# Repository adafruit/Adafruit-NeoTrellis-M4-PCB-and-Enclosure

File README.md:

# Adafruit-NeoTrellis-M4-PCB-and-Enclosure
CAD files for the Adafruit NeoTrellis M4 PCB and Enclosure

PCB format is EagleCAD schematic and board layout
Enclosure format is Illustrator, cut from 3mm Acrylic

For more details, check out the product pages at

   * https://www.adafruit.com/product/4020
   * https://www.adafruit.com/product/3938
   * https://www.adafruit.com/product/3963

Adafruit invests time and resources providing this open source design, 
please support Adafruit and open-source hardware by purchasing 
products from Adafruit!

Designed by Adafruit Industries.  
Creative Commons Attribution, Share-Alike license, check license.txt for more information
All text above must be included in any redistribution

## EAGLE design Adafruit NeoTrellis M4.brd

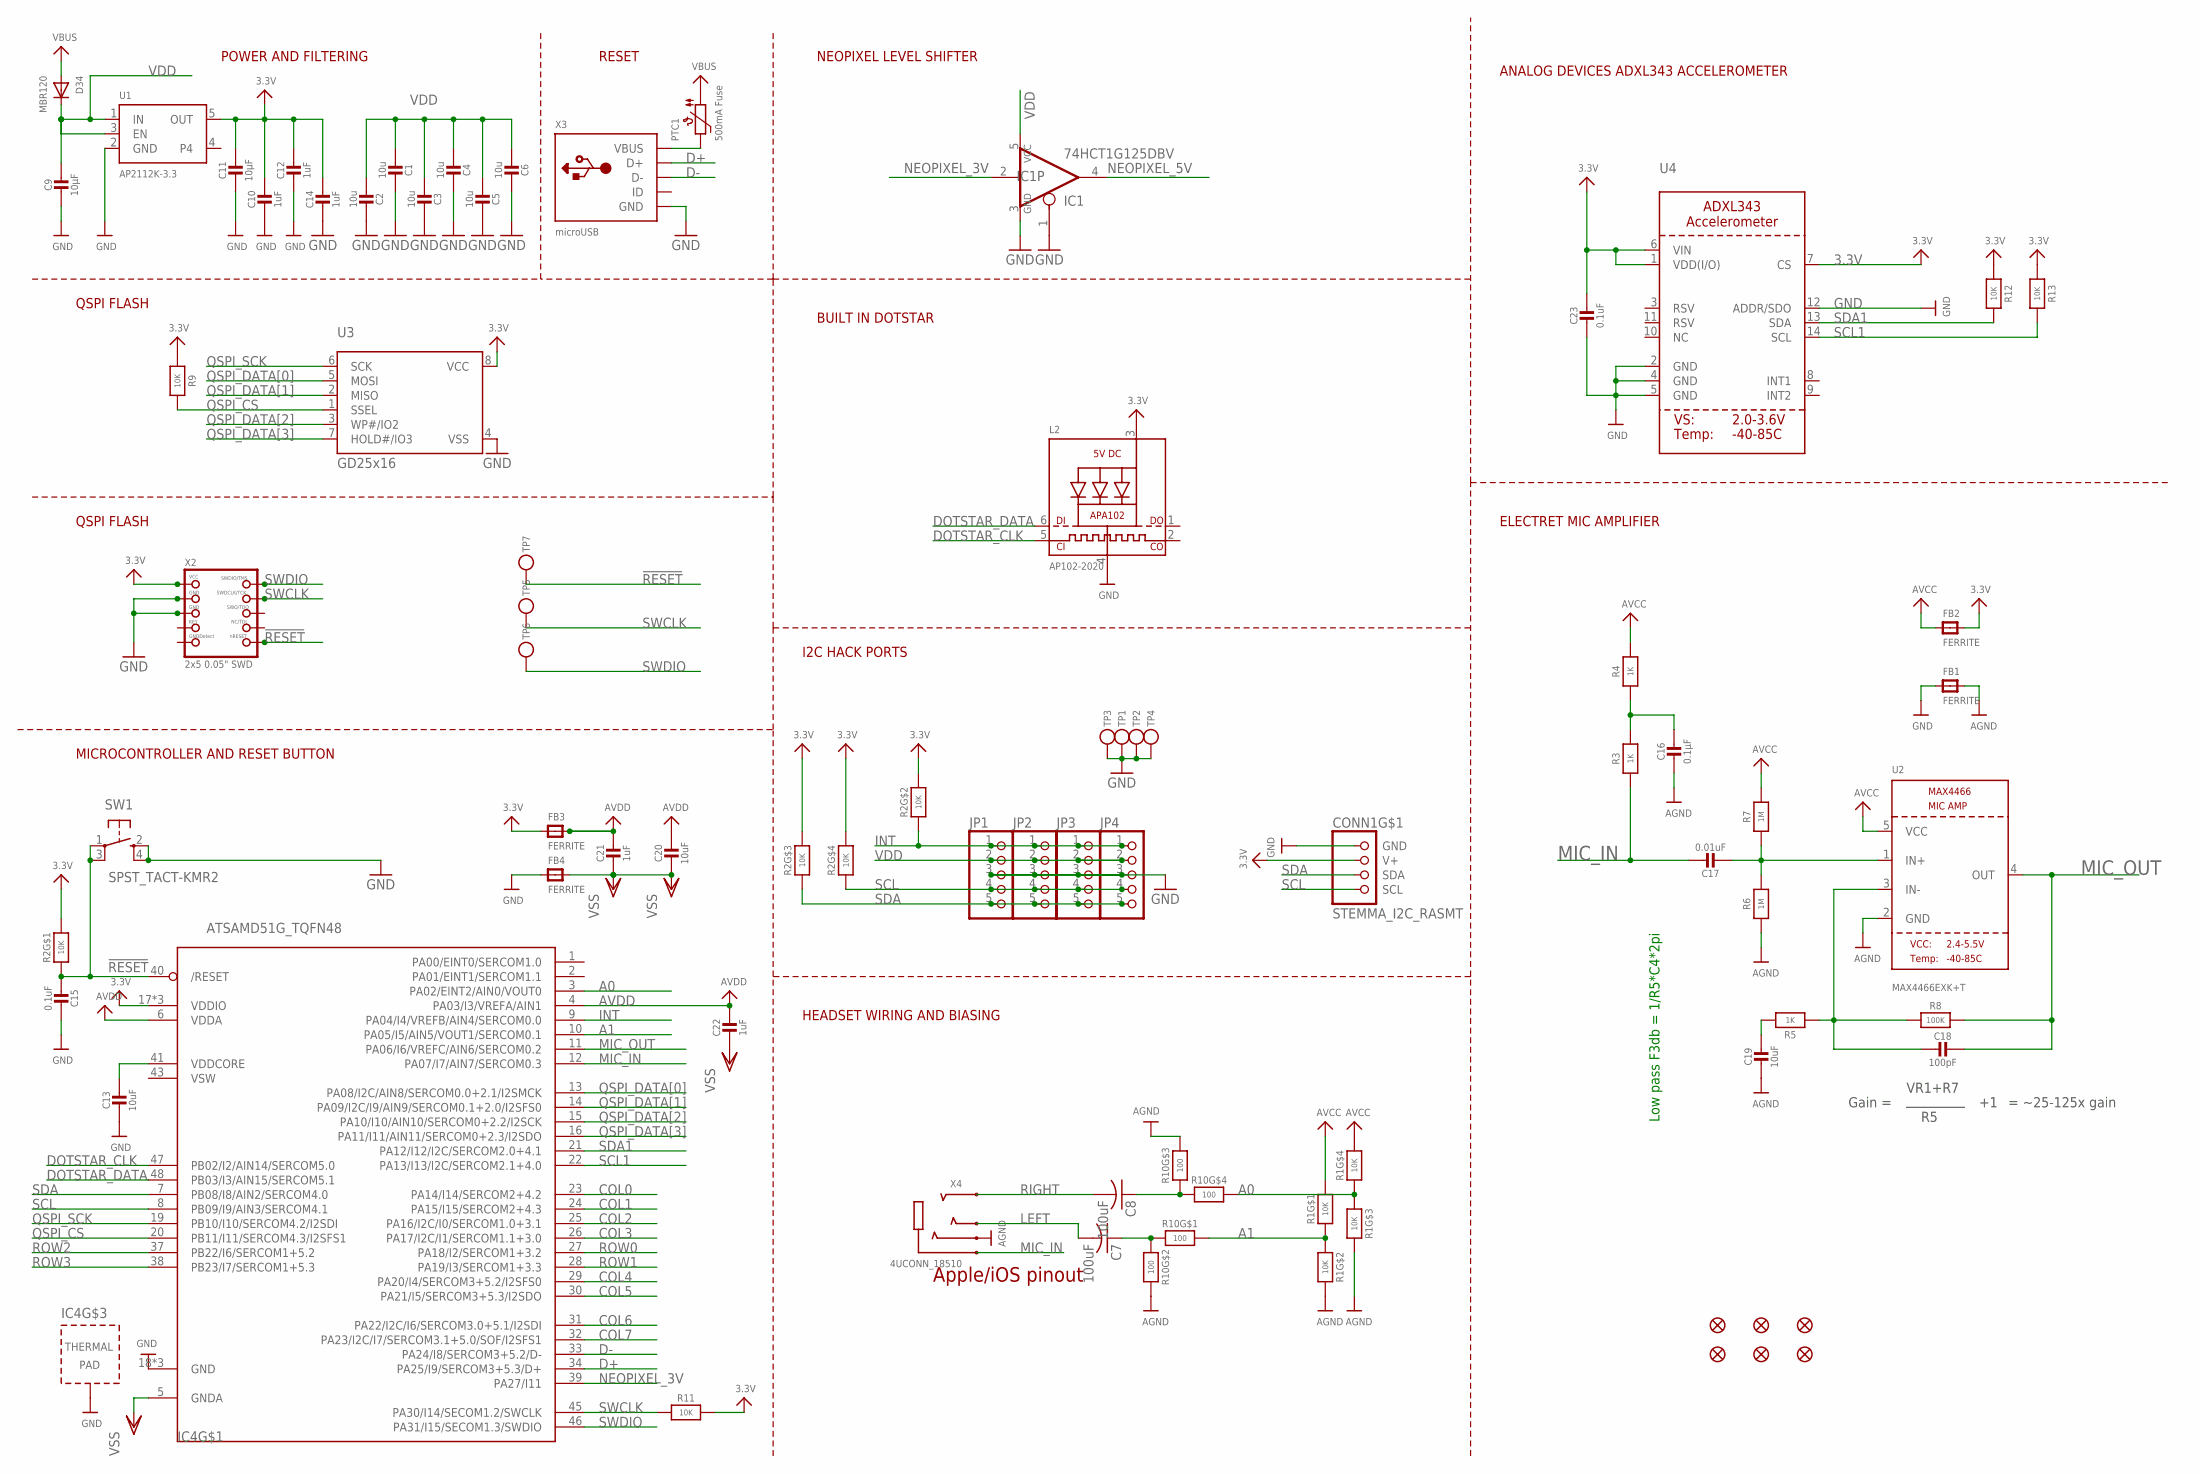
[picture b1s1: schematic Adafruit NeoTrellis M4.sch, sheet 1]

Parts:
C1, C2, C3, C4, C5, C6: 10u; 0805-NO
C7, C8: 100uF; C1210
C9, C11: 10µF; 0805-NO
C10, C12, C14, C21, C22: 1uF; 0603-NO
C13, C19, C20: 10uF; 0805-NO
C15, C23: 0.1uF; 0603-NO
C16: 0.1µF; 0603-NO
C17: 0.01uF; 0603-NO
C18: 100pF; 0603-NO
CONN1: STEMMA_I2C_RASMT; JSTPH4
D34: MBR120; SOD-123FL
FB1, FB2: FERRITE; 0805
FB3, FB4: FERRITE; 0805-NO
FID1, FID2, FID3, FID4, FID5, FID6: FIDUCIAL_1MM
IC1: 74HCT1G125DBV; SOT23-5
IC4: ATSAMD51G_TQFN48; TQFN48_7MM
JP1, JP2, JP3, JP4: HEADER-1X5EDGESMT; 5P_EDGECONNECT
L2: AP102-2020; APA102_2020
PTC1: 500mA Fuse; 1206
R1, R2: 10K; RESPACK_4X0603
R3, R4, R5: 1K; 0603-NO
R6, R7: 1M; 0603-NO
R8: 100K; 0603-NO
R9, R11, R12, R13: 10K; 0603-NO
R10: 100; RESPACK_4X0603
SW1: SPST_TACT-KMR2; KMR2
TP1, TP2, TP3, TP4: TESTPOINT; TESTPOINT_SMT
TP5, TP6: TESTPOINTROUND2MM; TESTPOINT_ROUND_2MM
TP7: TESTPOINTROUND1.5MM; TESTPOINT_ROUND_1.5MM
U1: AP2112K-3.3; SOT23-5
U2: MAX4466EXK+T; SC70-5
U3: GD25x16; SOIC8_208MIL
U4: ACCEL_ADXL343; LGA14
X2: 2x5 0.05" SWD; 2X05_1.27MM_BOX_POSTS
X3: microUSB; 4UCONN_20329_NARROW
X4: 4UCONN_18510

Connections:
3.3V: C10.1, C11.1, C12.1, C14.1, C23.1, CONN1.2 (V+), FB2.2, FB3.1, IC4.17 (VDDIO), IC4.36 (VDDIO), IC4.44 (VDDIO), L2.3 (VDD), R2.5 (2), R2.6 (2), R2.7 (2), R2.8 (2), R9.1, R11.2, R12.1, R13.1, U1.5 (OUT), U3.8 (VCC), U4.1 (VDD(I/O)), U4.6 (VIN), U4.7 (CS), X2.1 (VCC)
!RESET: C15.2, IC4.40 (/RESET), R2.1, SW1.1, SW1.3 (P1), TP7.P$1, X2.10 (NRESET)
A0: IC4.3 (PA02/EINT2/AIN0/VOUT0), R1.3 (1), R1.4 (1), R10.5 (2)
A1: IC4.10 (PA05/I5/AIN5/VOUT1/SERCOM0.1), R1.1, R1.2 (1), R10.8 (2)
AGND: C16.2, C19.2, FB1.2, R1.6 (2), R1.7 (2), R6.1, R10.6 (2), R10.7 (2), U2.2 (GND), X4.4-INNER_SLEEVE (RING1)
AVCC: FB2.1, R1.5 (2), R1.8 (2), R4.2, R7.2, U2.5 (VCC)
AVDD: C20.1, C21.1, C22.1, FB3.2, IC4.4 (PA03/I3/VREFA/AIN1), IC4.6 (VDDA)
COL0: IC4.23 (PA14/I14/SERCOM2+4.2); also elsewhere on the board
COL1: IC4.24 (PA15/I15/SERCOM2+4.3); also elsewhere on the board
COL2: IC4.25 (PA16/I2C/I0/SERCOM1.0+3.1); also elsewhere on the board
COL3: IC4.26 (PA17/I2C/I1/SERCOM1.1+3.0); also elsewhere on the board
COL4: IC4.29 (PA20/I4/SERCOM3+5.2/I2SFS0); also elsewhere on the board
COL5: IC4.30 (PA21/I5/SERCOM3+5.3/I2SDO); also elsewhere on the board
COL6: IC4.31 (PA22/I2C/I6/SERCOM3.0+5.1/I2SDI); also elsewhere on the board
COL7: IC4.32 (PA23/I2C/I7/SERCOM3.1+5.0/SOF/I2SFS1); also elsewhere on the board
D+: IC4.34 (PA25/I9/SERCOM3+5.3/D+), X3.D+
D-: IC4.33 (PA24/I8/SERCOM3+5.2/D-), X3.D-
DOTSTAR_CLK: IC4.47 (PB02/I2/AIN14/SERCOM5.0), L2.5 (CKI)
DOTSTAR_DATA: IC4.48 (PB03/I3/AIN15/SERCOM5.1), L2.6 (DI)
GND: C1.1, C2.1, C3.1, C4.1, C5.1, C6.1, C9.2, C10.2, C11.2, C12.2, C13.2, C14.2, C15.1, C23.2, CONN1.1 (GND), FB1.1, FB4.1, IC1.1 (OE), IC1.3 (GND), IC4.18 (GND), IC4.35 (GND), IC4.42 (GND), IC4.THERMAL (TP), JP1.3, JP2.3, JP3.3, JP4.3, L2.4 (GND), SW1.2 (S), SW1.4 (S1), TP1.P$1, TP2.P$1, TP3.P$1, TP4.P$1, U1.2 (GND), U3.4 (VSS), U4.2 (GND), U4.4 (GND), U4.5 (GND), U4.12 (ADDR/SDO), X2.3 (GND), X2.5 (GND), X3.BASE@1 (GND), X3.BASE@2 (GND), X3.GND, X3.SPRT@1 (GND), X3.SPRT@2 (GND), X3.SPRT@3 (GND), X3.SPRT@4 (GND); also elsewhere on the board
INT: IC4.9 (PA04/I4/VREFB/AIN4/SERCOM0.0), JP1.1, JP2.1, JP3.1, JP4.1, R2.2 (1)
LEFT: C7.2, X4.2-TIP (RING3)
MIC_IN: C17.1, IC4.12 (PA07/I7/AIN7/SERCOM0.3), R3.1, X4.1-GND (TIP)
MIC_OUT: C18.1, IC4.11 (PA06/I6/VREFC/AIN6/SERCOM0.2), R8.2, U2.4 (OUT)
unnamed: C8.1, R10.3 (1), R10.4 (1)
unnamed: C16.1, R3.2, R4.1
unnamed: PTC1.2, X3.VBUS
unnamed: C17.2, R6.2, R7.1, U2.1 (IN+)
unnamed: C18.2, R5.1, R8.1, U2.3 (IN-)
unnamed: C19.1, R5.2
unnamed: C7.1, R10.1, R10.2 (1)
NEOPIXEL_3V: IC1.2 (I), IC4.39 (PA27/I11)
NEOPIXEL_5V: IC1.4 (O); also elsewhere on the board
QSPI_CS: IC4.20 (PB11/I11/SERCOM4.3/I2SFS1), R9.2, U3.1 (SSEL)
QSPI_DATA[0]: IC4.13 (PA08/I2C/AIN8/SERCOM0.0+2.1/I2SMCK), U3.5 (MOSI)
QSPI_DATA[1]: IC4.14 (PA09/I2C/I9/AIN9/SERCOM0.1+2.0/I2SFS0), U3.2 (MISO)
QSPI_DATA[2]: IC4.15 (PA10/I10/AIN10/SERCOM0+2.2/I2SCK), U3.3 (WP#/IO2)
QSPI_DATA[3]: IC4.16 (PA11/I11/AIN11/SERCOM0+2.3/I2SDO), U3.7 (HOLD#/IO3)
QSPI_SCK: IC4.19 (PB10/I10/SERCOM4.2/I2SDI), U3.6 (SCK)
RIGHT: C8.2, X4.3-OUTER_SLEEVE (RING2)
ROW0: IC4.27 (PA18/I2/SERCOM1+3.2); also elsewhere on the board
ROW1: IC4.28 (PA19/I3/SERCOM1+3.3); also elsewhere on the board
ROW2: IC4.37 (PB22/I6/SERCOM1+5.2); also elsewhere on the board
ROW3: IC4.38 (PB23/I7/SERCOM1+5.3); also elsewhere on the board
SCL: CONN1.4 (SCL), IC4.8 (PB09/I9/AIN3/SERCOM4.1), JP1.4, JP2.4, JP3.4, JP4.4, R2.4 (1)
SCL1: IC4.22 (PA13/I13/I2C/SERCOM2.1+4.0), R13.2, U4.14 (SCL)
SDA: CONN1.3 (SDA), IC4.7 (PB08/I8/AIN2/SERCOM4.0), JP1.5, JP2.5, JP3.5, JP4.5, R2.3 (1)
SDA1: IC4.21 (PA12/I12/I2C/SERCOM2.0+4.1), R12.2, U4.13 (SDA)
SWCLK: IC4.45 (PA30/I14/SECOM1.2/SWCLK), R11.1, TP5.P$1, X2.4 (SWDCLK)
SWDIO: IC4.46 (PA31/I15/SECOM1.3/SWDIO), TP6.P$1, X2.2 (SWDIO)
VBUS: D34.A, PTC1.1
VDD: C1.2, C2.2, C3.2, C4.2, C5.2, C6.2, C9.1, D34.C, IC1.5 (VCC), JP1.2, JP2.2, JP3.2, JP4.2, U1.1 (IN), U1.3 (EN); also elsewhere on the board
VDDCORE: C13.1, IC4.41 (VDDCORE)
VSS: C20.2, C21.2, C22.2, FB4.2, IC4.5 (GNDA)
VSW: IC4.43 (VSW)

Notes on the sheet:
POWER AND FILTERING
RESET
Apple/iOS pinout
Gain =
VR1+R7
= ~25-125x gain
Low pass F3db = 1/R5*C4*2pi
NEOPIXEL LEVEL SHIFTER
BUILT IN DOTSTAR
I2C HACK PORTS
HEADSET WIRING AND BIASING
QSPI FLASH
MICROCONTROLLER AND RESET BUTTON
ELECTRET MIC AMPLIFIER
ANALOG DEVICES ADXL343 ACCELEROMETER

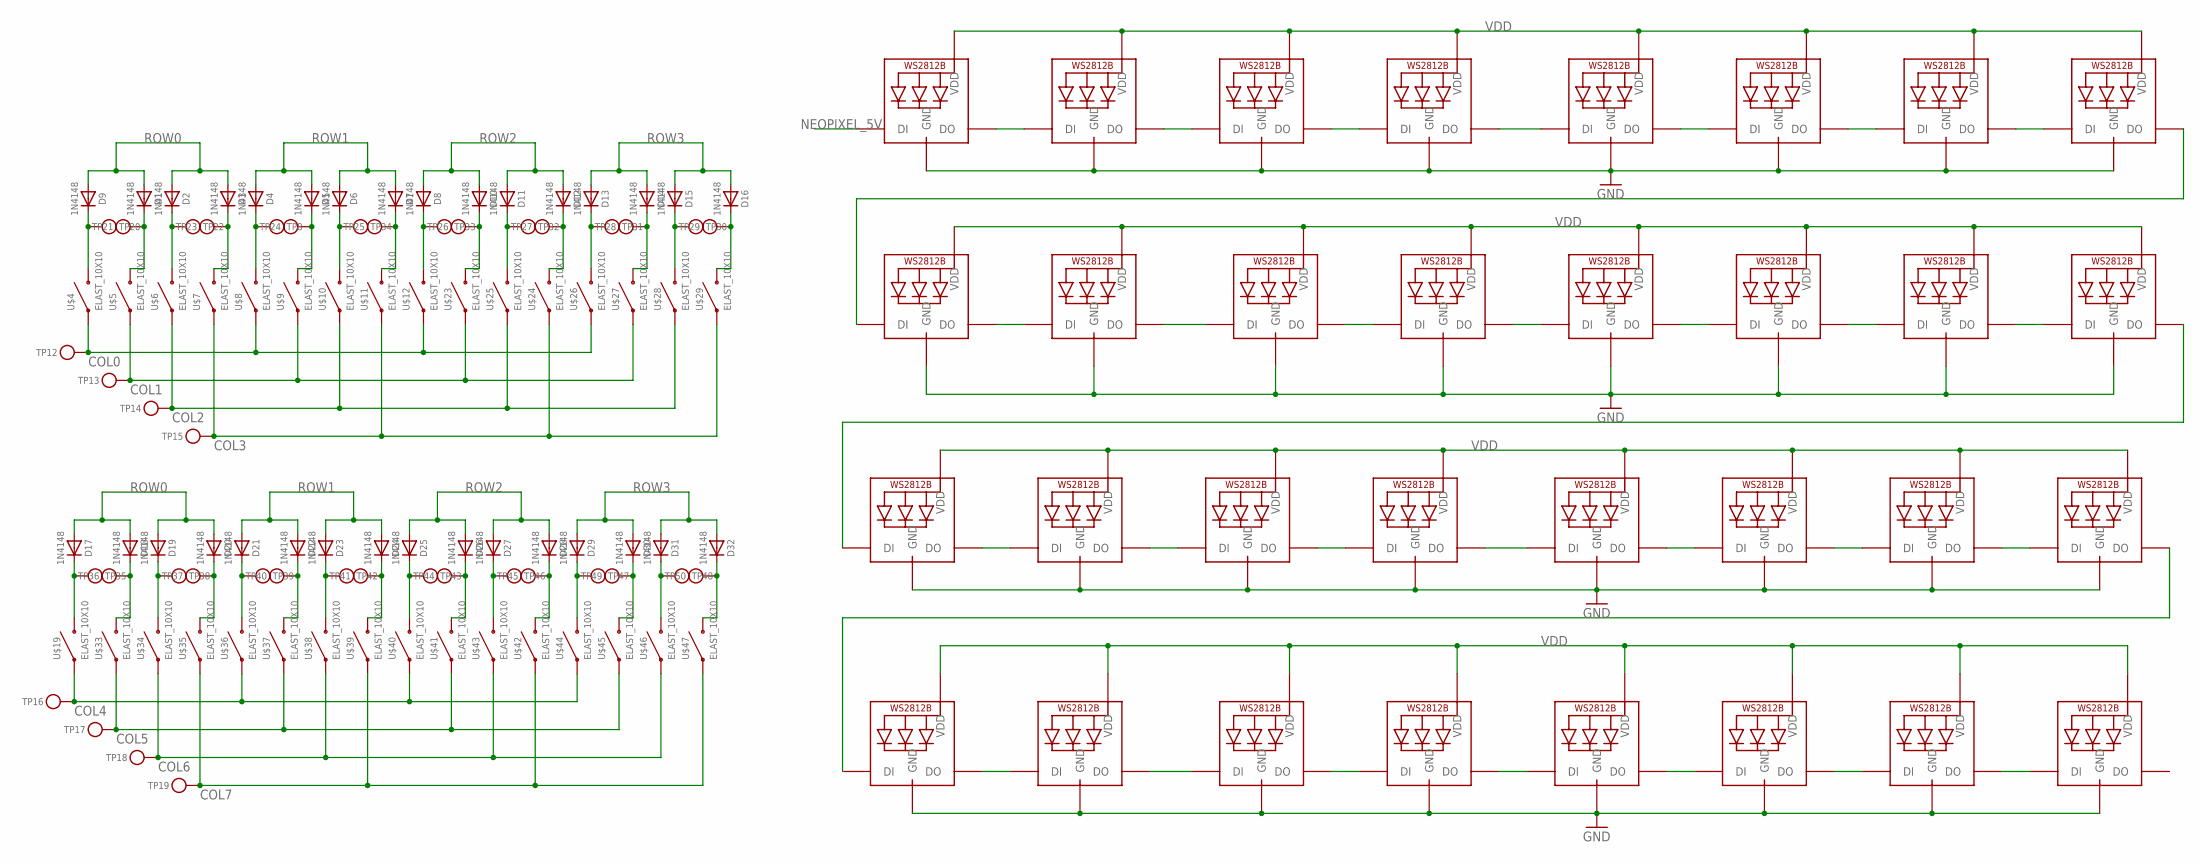
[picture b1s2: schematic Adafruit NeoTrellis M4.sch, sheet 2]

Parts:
D1, D2, D3, D4, D5, D6, D7, D8, D9, D10, D11, D12, D13, D14, D15, D16, D17, D18, D19, D20, D21, D22, D23, D24, D25, D26, D27, D28, D29, D30, D31, D32: 1N4148; SOD-323
LED1, LED2, LED3, LED4, LED5, LED6, LED7, LED8, LED9, LED10, LED11, LED12, LED13, LED14, LED15, LED16, LED17, LED18, LED19, LED20, LED21, LED22, LED23, LED24, LED25, LED26, LED27, LED28, LED29, LED30, LED31, LED32: WS2812B3535; LED3535
TP8, TP12, TP13, TP14, TP15, TP16, TP17, TP18, TP19, TP20, TP21, TP22, TP23, TP24, TP25, TP26, TP27, TP28, TP29, TP30, TP31, TP32, TP33, TP34, TP35, TP36, TP37, TP38, TP39, TP40, TP41, TP42, TP43, TP44, TP45, TP46, TP47, TP48, TP49, TP50: TESTPOINTROUND1.5MM; TESTPOINT_ROUND_1.5MM
U$4, U$5, U$6, U$7, U$8, U$9, U$10, U$11, U$12, U$19, U$23, U$24, U$25, U$26, U$27, U$28, U$29, U$33, U$34, U$35, U$36, U$37, U$38, U$39, U$40, U$41, U$42, U$43, U$44, U$45, U$46, U$47: ELAST_10X10; ELAST_PAD_SQUARE_10MM_4X4WIDE

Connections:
COL0: TP12.P$1, U$4.P$1, U$8.P$1, U$12.P$1, U$26.P$1; also elsewhere on the board
COL1: TP13.P$1, U$5.P$1, U$9.P$1, U$23.P$1, U$27.P$1; also elsewhere on the board
COL2: TP14.P$1, U$6.P$1, U$10.P$1, U$25.P$1, U$28.P$1; also elsewhere on the board
COL3: TP15.P$1, U$7.P$1, U$11.P$1, U$24.P$1, U$29.P$1; also elsewhere on the board
COL4: TP16.P$1, U$19.P$1, U$36.P$1, U$40.P$1, U$44.P$1; also elsewhere on the board
COL5: TP17.P$1, U$33.P$1, U$37.P$1, U$41.P$1, U$45.P$1; also elsewhere on the board
COL6: TP18.P$1, U$34.P$1, U$38.P$1, U$43.P$1, U$46.P$1; also elsewhere on the board
COL7: TP19.P$1, U$35.P$1, U$39.P$1, U$42.P$1, U$47.P$1; also elsewhere on the board
GND: LED1.4 (GND), LED2.4 (GND), LED3.4 (GND), LED4.4 (GND), LED5.4 (GND), LED6.4 (GND), LED7.4 (GND), LED8.4 (GND), LED9.4 (GND), LED10.4 (GND), LED11.4 (GND), LED12.4 (GND), LED13.4 (GND), LED14.4 (GND), LED15.4 (GND), LED16.4 (GND), LED17.4 (GND), LED18.4 (GND), LED19.4 (GND), LED20.4 (GND), LED21.4 (GND), LED22.4 (GND), LED23.4 (GND), LED24.4 (GND), LED25.4 (GND), LED26.4 (GND), LED27.4 (GND), LED28.4 (GND), LED29.4 (GND), LED30.4 (GND), LED31.4 (GND), LED32.4 (GND); also elsewhere on the board
unnamed: D9.C, TP20.P$1, U$4.P$2
unnamed: D1.C, TP21.P$1, U$5.P$2
unnamed: D2.C, TP22.P$1, U$6.P$2
unnamed: D3.C, TP23.P$1, U$7.P$2
unnamed: D4.C, TP8.P$1, U$8.P$2
unnamed: LED17.3 (DO), LED18.1 (DI)
unnamed: LED18.3 (DO), LED19.1 (DI)
unnamed: D5.C, TP24.P$1, U$9.P$2
unnamed: LED19.3 (DO), LED20.1 (DI)
unnamed: LED1.3 (DO), LED2.1 (DI)
unnamed: LED2.3 (DO), LED3.1 (DI)
unnamed: LED3.3 (DO), LED4.1 (DI)
unnamed: LED4.3 (DO), LED5.1 (DI)
unnamed: D6.C, TP34.P$1, U$10.P$2
unnamed: LED5.3 (DO), LED6.1 (DI)
unnamed: LED6.3 (DO), LED7.1 (DI)
unnamed: D7.C, TP25.P$1, U$11.P$2
unnamed: LED7.3 (DO), LED8.1 (DI)
unnamed: D8.C, TP33.P$1, U$12.P$2
unnamed: LED8.3 (DO), LED9.1 (DI)
unnamed: D10.C, TP26.P$1, U$23.P$2
unnamed: D11.C, TP32.P$1, U$25.P$2
unnamed: D12.C, TP27.P$1, U$24.P$2
unnamed: D13.C, TP31.P$1, U$26.P$2
unnamed: D14.C, TP28.P$1, U$27.P$2
unnamed: D15.C, TP30.P$1, U$28.P$2
unnamed: D16.C, TP29.P$1, U$29.P$2
unnamed: LED9.3 (DO), LED10.1 (DI)
unnamed: LED10.3 (DO), LED12.1 (DI)
unnamed: LED11.1 (DI), LED12.3 (DO)
unnamed: LED11.3 (DO), LED13.1 (DI)
unnamed: LED13.3 (DO), LED14.1 (DI)
unnamed: LED14.3 (DO), LED15.1 (DI)
unnamed: LED15.3 (DO), LED16.1 (DI)
unnamed: LED20.3 (DO), LED21.1 (DI)
unnamed: LED21.3 (DO), LED22.1 (DI)
unnamed: LED22.3 (DO), LED23.1 (DI)
unnamed: LED23.3 (DO), LED24.1 (DI)
unnamed: LED24.3 (DO), LED25.1 (DI)
unnamed: LED25.3 (DO), LED26.1 (DI)
unnamed: LED26.3 (DO), LED28.1 (DI)
unnamed: LED27.1 (DI), LED28.3 (DO)
unnamed: LED27.3 (DO), LED29.1 (DI)
unnamed: LED29.3 (DO), LED30.1 (DI)
unnamed: LED30.3 (DO), LED31.1 (DI)
unnamed: LED31.3 (DO), LED32.1 (DI)
unnamed: D17.C, TP35.P$1, U$19.P$2
unnamed: D18.C, TP36.P$1, U$33.P$2
unnamed: D19.C, TP38.P$1, U$34.P$2
unnamed: D20.C, TP37.P$1, U$35.P$2
unnamed: D21.C, TP39.P$1, U$36.P$2
unnamed: D22.C, TP40.P$1, U$37.P$2
unnamed: D23.C, TP42.P$1, U$38.P$2
unnamed: D24.C, TP41.P$1, U$39.P$2
unnamed: D25.C, TP43.P$1, U$40.P$2
unnamed: D26.C, TP44.P$1, U$41.P$2
unnamed: D27.C, TP46.P$1, U$43.P$2
unnamed: D28.C, TP45.P$1, U$42.P$2
unnamed: D29.C, TP47.P$1, U$44.P$2
unnamed: D30.C, TP49.P$1, U$45.P$2
unnamed: D31.C, TP48.P$1, U$46.P$2
unnamed: D32.C, TP50.P$1, U$47.P$2
unnamed: LED16.3 (DO), LED17.1 (DI)
NEOPIXEL_5V: LED1.1 (DI); also elsewhere on the board
ROW0: D1.A, D2.A, D3.A, D9.A, D17.A, D18.A, D19.A, D20.A; also elsewhere on the board
ROW1: D4.A, D5.A, D6.A, D7.A, D21.A, D22.A, D23.A, D24.A; also elsewhere on the board
ROW2: D8.A, D10.A, D11.A, D12.A, D25.A, D26.A, D27.A, D28.A; also elsewhere on the board
ROW3: D13.A, D14.A, D15.A, D16.A, D29.A, D30.A, D31.A, D32.A; also elsewhere on the board
VDD: LED1.2 (VDD), LED2.2 (VDD), LED3.2 (VDD), LED4.2 (VDD), LED5.2 (VDD), LED6.2 (VDD), LED7.2 (VDD), LED8.2 (VDD), LED9.2 (VDD), LED10.2 (VDD), LED11.2 (VDD), LED12.2 (VDD), LED13.2 (VDD), LED14.2 (VDD), LED15.2 (VDD), LED16.2 (VDD), LED17.2 (VDD), LED18.2 (VDD), LED19.2 (VDD), LED20.2 (VDD), LED21.2 (VDD), LED22.2 (VDD), LED23.2 (VDD), LED24.2 (VDD), LED25.2 (VDD), LED26.2 (VDD), LED27.2 (VDD), LED28.2 (VDD), LED29.2 (VDD), LED30.2 (VDD), LED31.2 (VDD), LED32.2 (VDD); also elsewhere on the board

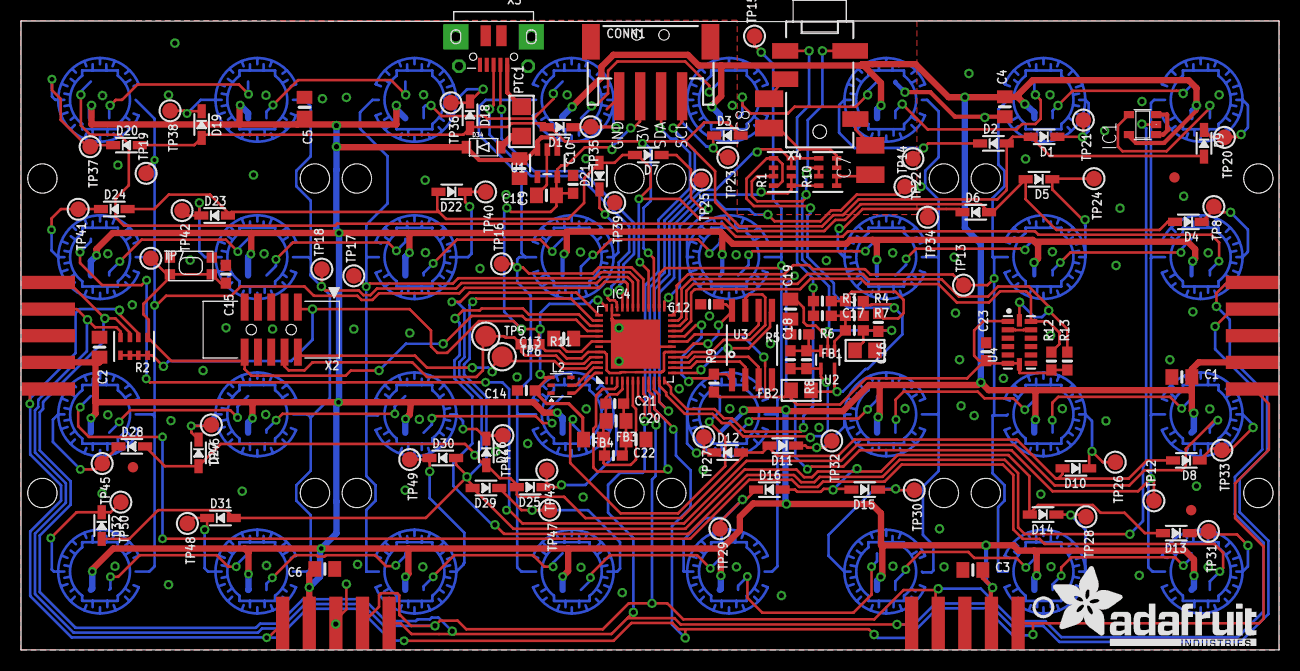
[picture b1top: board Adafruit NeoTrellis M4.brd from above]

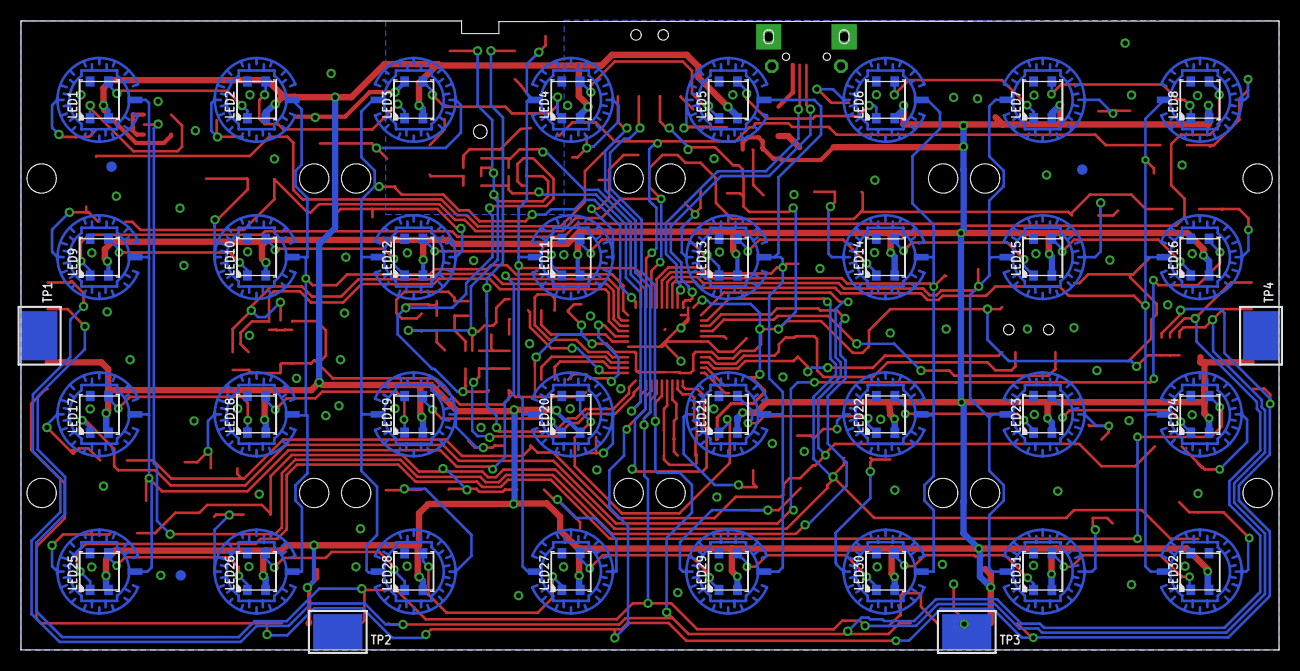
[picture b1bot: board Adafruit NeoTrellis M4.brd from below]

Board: 2 copper layers, 120.0 x 60.0 mm, 210 parts (71 on the bottom side), 117 nets.

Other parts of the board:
U$3: ADAFRUIT_TEXT_20MM
U$48: TRELLISLOGO
U$78: PCBFEAT-REV-040

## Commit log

2018-11-04 init
2022-06-06 Added Prettypins

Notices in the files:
parts and their libraries:
microbuilder: This work is placed in the public domain, and may be freely used for commercial and non-commercial work with the following conditions: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
